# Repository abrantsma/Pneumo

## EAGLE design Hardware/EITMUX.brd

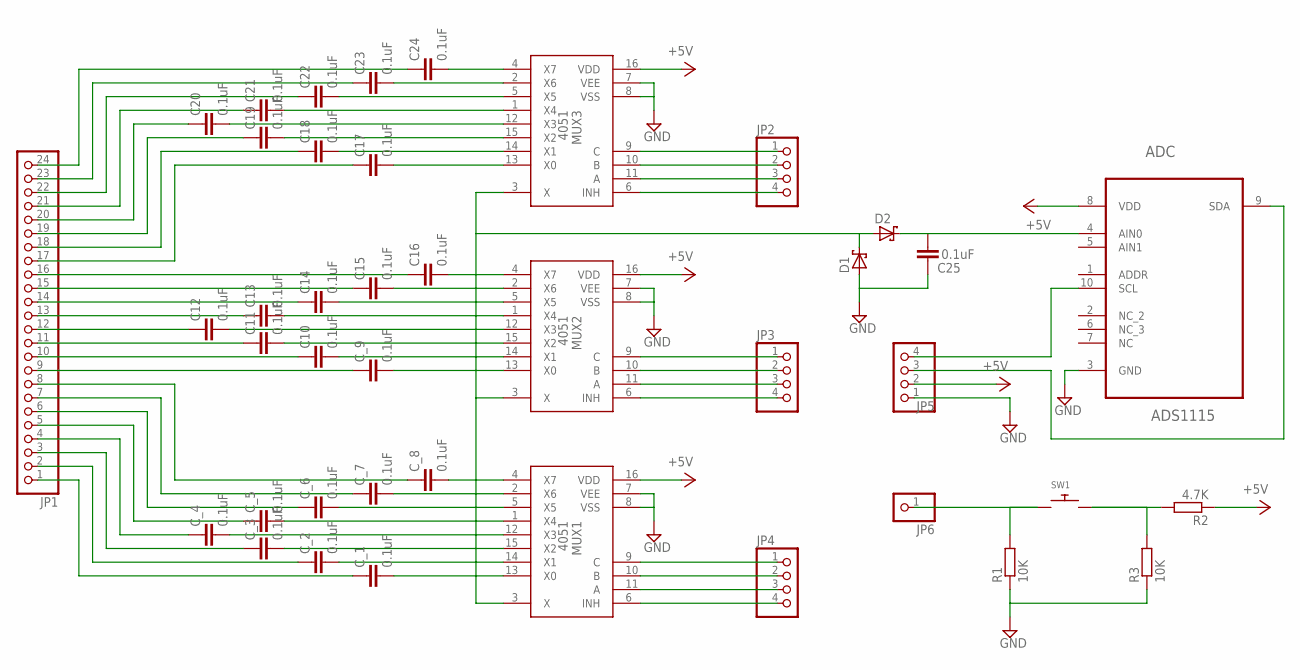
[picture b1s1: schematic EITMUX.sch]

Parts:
ADC: ADS1115; SOP50P490X110-10N
C10, C11, C12, C13, C14, C15, C16, C17, C18, C19, C20, C21, C22, C23, C24, C25: 0.1uF; C0603
C_1, C_2, C_3, C_4, C_5, C_6, C_7, C_8, C_9: 0.1uF; C0603
D1, D2: SCHOTTKY-DIODEDO35-7; DIODE_DO35-7
JP1: PINHD-1X24; 1X24
JP2, JP3, JP4, JP5: PINHD-1X4; 1X04
JP6: PINHD-1X1; 1X01
MUX1, MUX2, MUX3: 4051; DIL16
R1, R3: 10K; R0603
R2: 4.7K; R0603
SW1: SWITCH_PUSHBUTTONEVQ-PE; TACT_PANA-EVQ

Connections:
+5V: ADC.8 (VDD), JP5.2, MUX1.16 (VDD), MUX2.16 (VDD), MUX3.16 (VDD), R2.1
C_11: C10.1, JP1.10
C_12: C11.1, JP1.11
GND: ADC.3 (GND), C25.1, D1.A (C), JP5.1, MUX1.7 (VEE), MUX1.8 (VSS), MUX2.7 (VEE), MUX2.8 (VSS), MUX3.7 (VEE), MUX3.8 (VSS), R1.1, R3.1
unnamed: C20.2, MUX3.12 (X3)
unnamed: C19.2, MUX3.15 (X2)
unnamed: C18.2, MUX3.14 (X1)
unnamed: C17.2, MUX3.13 (X0)
unnamed: C16.2, MUX2.4 (X7)
unnamed: C15.2, MUX2.2 (X6)
unnamed: C14.2, MUX2.5 (X5)
unnamed: C13.2, MUX2.1 (X4)
unnamed: C12.2, MUX2.12 (X3)
unnamed: C11.2, MUX2.15 (X2)
unnamed: C10.2, MUX2.14 (X1)
unnamed: C_9.2, MUX2.13 (X0)
unnamed: C_8.2, MUX1.4 (X7)
unnamed: C_7.2, MUX1.2 (X6)
unnamed: C_6.2, MUX1.5 (X5)
unnamed: C_5.2, MUX1.1 (X4)
unnamed: C_4.2, MUX1.12 (X3)
unnamed: C_3.2, MUX1.15 (X2)
unnamed: C_2.2, MUX1.14 (X1)
unnamed: C_1.2, MUX1.13 (X0)
unnamed: D1.C (A), D2.A (C), MUX1.3 (X), MUX2.3 (X), MUX3.3 (X)
unnamed: C24.2, MUX3.4 (X7)
unnamed: C23.2, MUX3.2 (X6)
unnamed: C22.2, MUX3.5 (X5)
unnamed: C_1.1, JP1.1
unnamed: C_2.1, JP1.2
unnamed: C_3.1, JP1.3
unnamed: C_4.1, JP1.4
unnamed: C_5.1, JP1.5
unnamed: C_6.1, JP1.6
unnamed: C_7.1, JP1.7
unnamed: C_8.1, JP1.8
unnamed: C_9.1, JP1.9
unnamed: JP6.1, R1.2, SW1.P$1
unnamed: R2.2, R3.2, SW1.P$2
unnamed: C12.1, JP1.12
unnamed: C13.1, JP1.13
unnamed: C14.1, JP1.14
unnamed: C15.1, JP1.15
unnamed: C16.1, JP1.16
unnamed: C20.1, JP1.20
unnamed: C19.1, JP1.19
unnamed: C18.1, JP1.18
unnamed: C17.1, JP1.17
unnamed: C21.2, MUX3.1 (X4)
unnamed: C21.1, JP1.21
unnamed: C22.1, JP1.22
unnamed: C23.1, JP1.23
unnamed: C24.1, JP1.24
unnamed: JP2.1, MUX3.9 (C)
unnamed: JP2.2, MUX3.10 (B)
unnamed: JP2.3, MUX3.11 (A)
unnamed: JP2.4, MUX3.6 (INH)
unnamed: JP3.1, MUX2.9 (C)
unnamed: JP3.2, MUX2.10 (B)
unnamed: JP3.3, MUX2.11 (A)
unnamed: JP3.4, MUX2.6 (INH)
unnamed: JP4.1, MUX1.9 (C)
unnamed: JP4.2, MUX1.10 (B)
unnamed: JP4.3, MUX1.11 (A)
unnamed: JP4.4, MUX1.6 (INH)
unnamed: ADC.4 (AIN0), C25.2, D2.C (A)
unnamed: ADC.10 (SCL), JP5.4
unnamed: ADC.9 (SDA), JP5.3

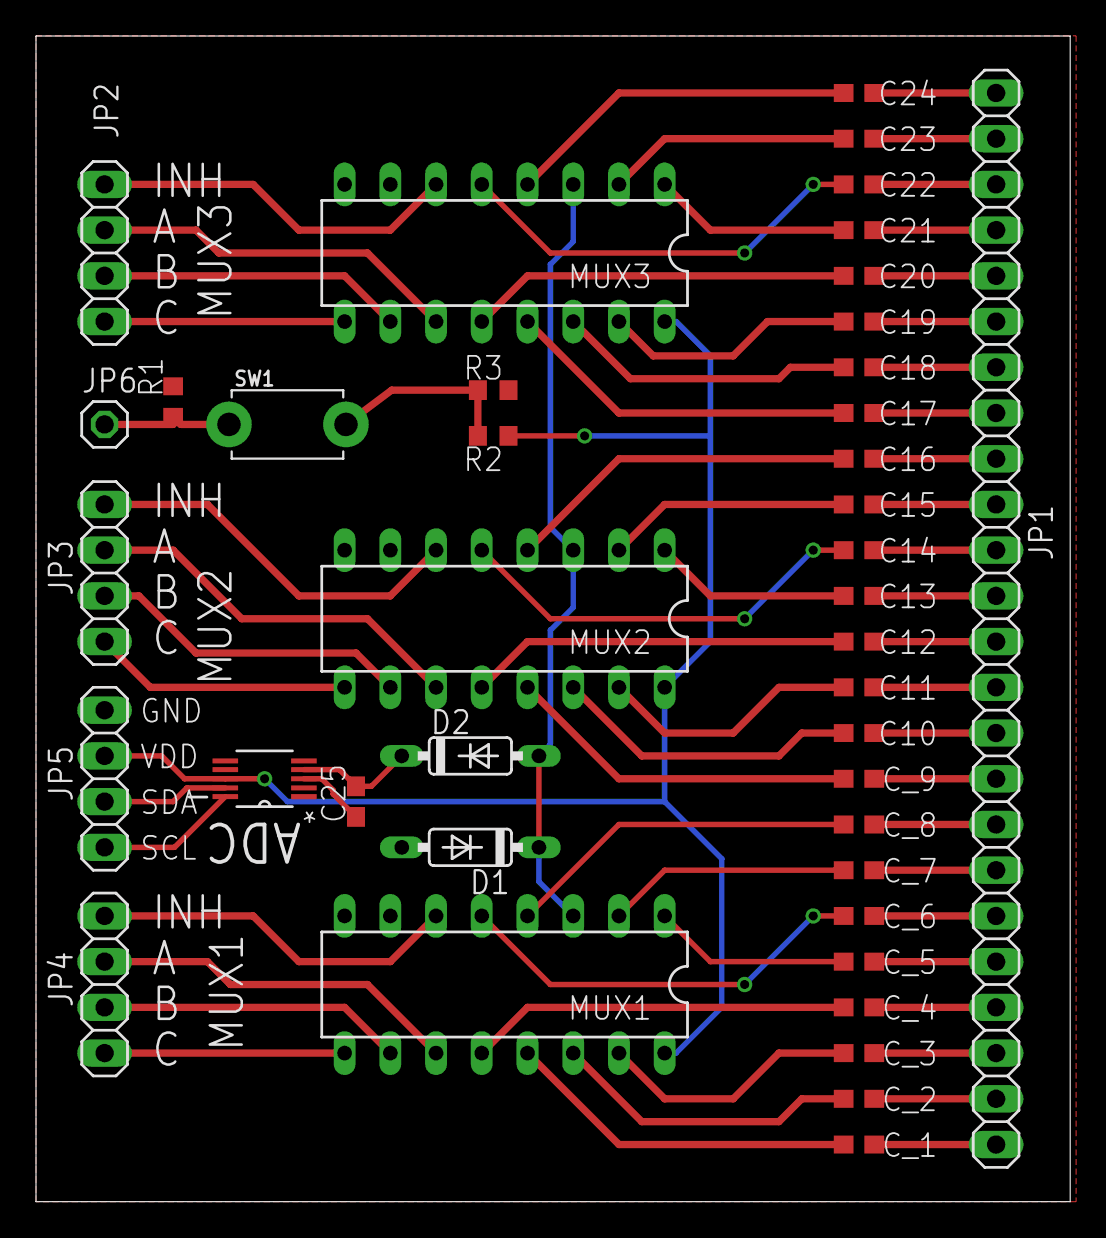
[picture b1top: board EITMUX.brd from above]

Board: 2 copper layers, 57.5 x 64.8 mm, 41 parts (0 on the bottom side), 68 nets.

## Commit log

2015-10-29 added absolute and difference files
2015-10-29 added marble coordinates function
2015-10-29 data gen corrections
2015-10-30 several important corrections and new files
2015-10-30 added more to difference and absolute scripts
2015-11-18 Many new things, mostly importantly including the imageReconstruction_v1.m file
2015-11-23 Added new reconstruction function
2015-12-03 added files for Octave
2015-12-03 updated csv files and added .m files
2015-12-07 added hardware files
2016-03-07 testing moving old stuff to a folder
2016-03-08 Added tic() and toc()s to _v4.m to make _v4t.m
2016-03-08 added variables for tocs
2016-03-08 Created and saved the common model imdl structure as common_model1 and created v5t.m which uses it.
2016-03-08 Reduce runtime by pre-sizing target matrix before for loop
2016-03-09 Parralelized the two for-loops that were taking forever so that they use four cores on those operations instead of one.
2016-03-09 Saved the status of the v4.m script when its done running for quick comparisons.
2016-03-09 Added v5tr.m which uses parallel cluster computing of two rpis to achieve a runtime of 711 seconds.
2016-03-27 move files to old folder
2016-03-27 moved more files to old folder
2016-03-31 move common model1 back to original folder
2016-04-03 move back to original folder
2016-04-27 Code to operate mux and ADC

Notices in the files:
parts and their libraries:
eagle-6.5.0-atari: Copyright (c) 2010
Copyright (c) 2009
This library is licensed under the
Creative Commons Attribution 3.0 United States License.
